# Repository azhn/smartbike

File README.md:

SMARTBIKE
=====

BLEES: Bluetooth Low Energy Environment Sensors.
<br /><br />
BLEES is a 1 inch round sensor tag for sensing the ambient environment. It monitors
temperature, humidity, light, pressure, and movement and reports its readings
over BLE.
<br /><br /><br />

Hardware
--------
The BLEES hardware is a small, once inch round sensor board that mounts onto a [Squall](https://github.com/helena-project/squall) BLE sensor tag. The board 
currently has four sensors:

1. Temperature and Humidity
2. Pressure
3. Light
4. Accelerometer

The BLEES hardware is located in the `hardware` directory, where you can find
the Eagle design files.

Software
--------
The [Squall](https://github.com/helena-project/squall) uses the software located 
in the `software` directory. Follow the directions at [Lab11's Wiki](http://lab11.eecs.umich.edu/wiki/doku.php?id=eecs582w15:setup:start) to 
get your machine set up to build and flash the Squall.

The software sends out the data from the BLEES sensors in BLE advertisements. Specifically,
we encode the data in the "manufacturer data" section of a BLE advertisement and scan response packet.
This means that we do not have to establish a connection between the Squall and a scanning device, 
saving energy by not requiring any devices to pair with the BLEES device, and allowing us to send
the sensor data to many different scanning devices at once.

[Here's a useful BLE Advertisement primer](http://www.argenox.com/bluetooth-low-energy-ble-v4-0-development/library/a-ble-advertising-primer/)

Summon App
-----------
[Summon](https://github.com/lab11/summon) is a UI application for BLE devices.
Rather than requiring every user
to install a new app for every BLE device, Summon allows BLE devices to
point to their own HTML/JS based interface and loads it in a single
application. BLEES supports the summon architecture and provides
a Summon application.

Cloning
-------
To clone both this repository and the required submodules,
clone with the `--recursive` option: 
`git clone --recursive git@github.com:lab11/blees.git`

Otherwise, you can initialize the submodule and keep submodules up to
date by doing `git submodule update --init --recursive`.

If you think all of this is ridiculous and git should just handle submodules automatically, use this:
https://gist.github.com/brghena/fc4483a2df83c47660a5

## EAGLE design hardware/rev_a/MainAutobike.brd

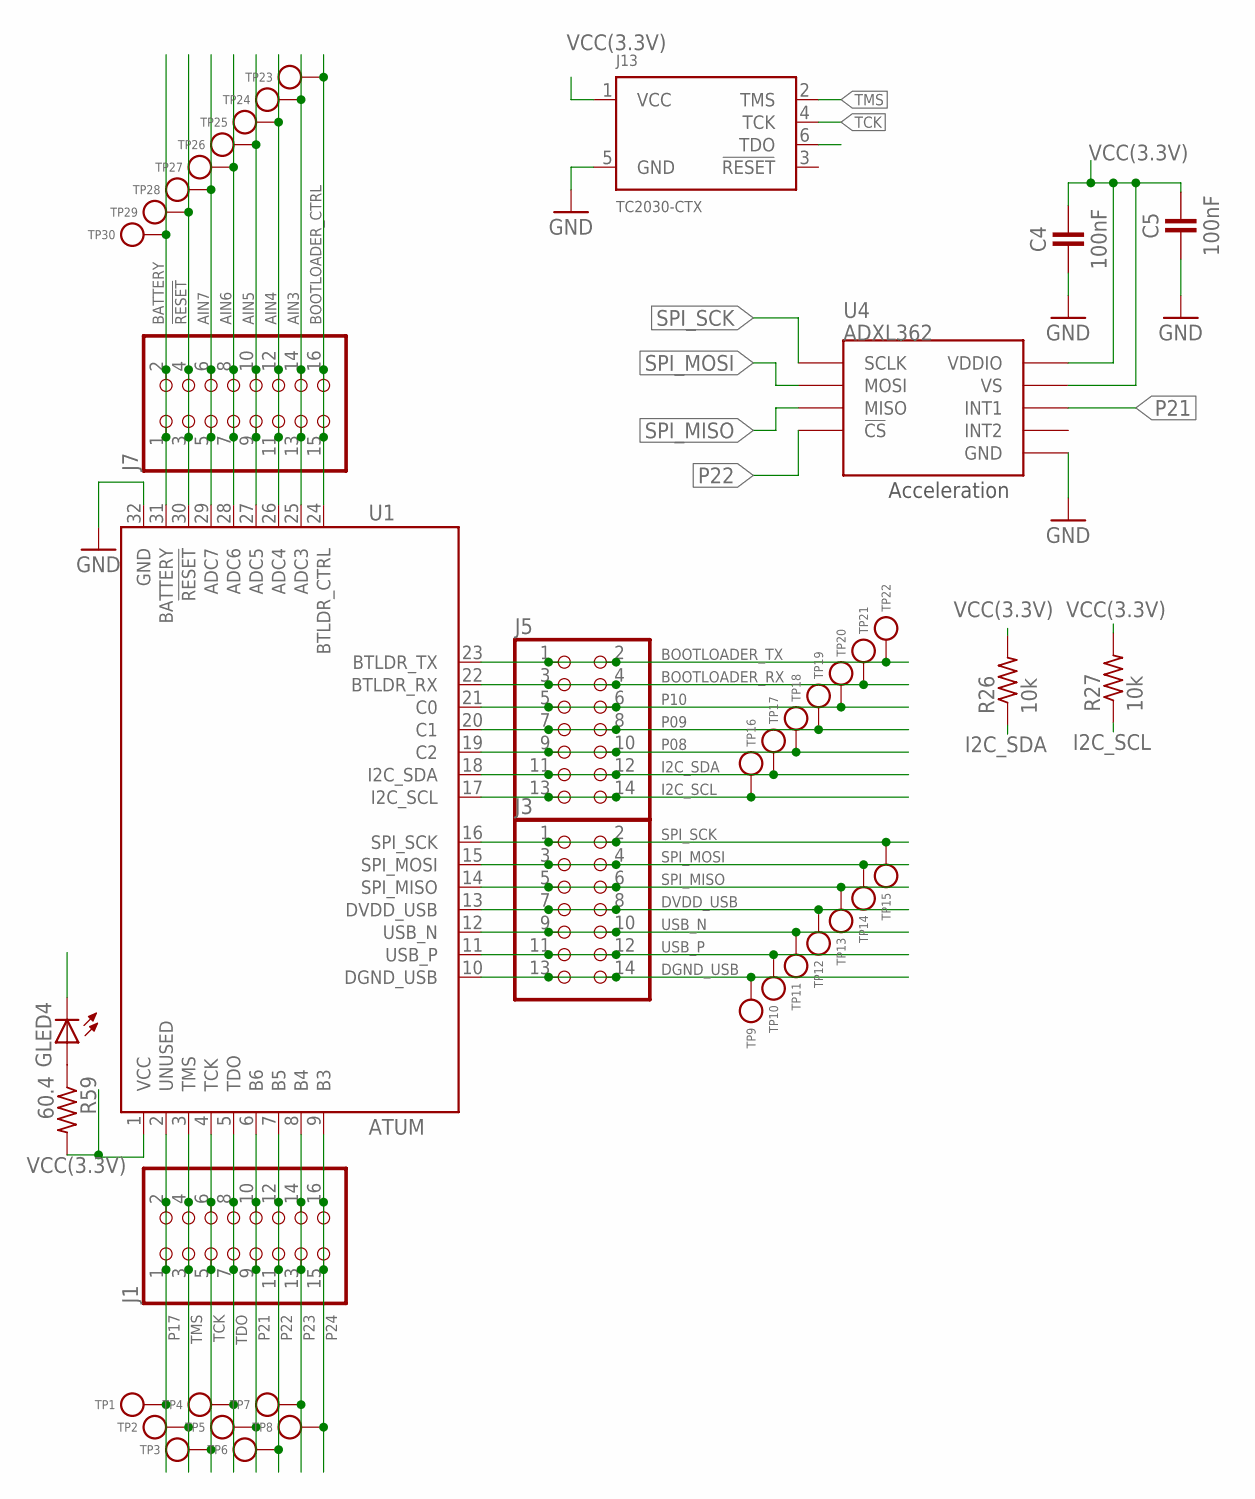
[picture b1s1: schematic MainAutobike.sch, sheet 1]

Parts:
C4, C5: 100nF; 0402_CAP
GLED4: LEDCHIP-LED0603; CHIP-LED0603
J1, J7: PINHD-2X8; 2X08; DIGIKEY 609-3364-ND
J3, J5: PINHD-2X7; 2X07; DIGIKEY 609-3491-ND
J13: TC2030-CTX; TC2030-IDC
R26, R27: 10k; R0603
R59: 60.4; R0402
TP1, TP2, TP3, TP4, TP5, TP6, TP7, TP8, TP9, TP10, TP11, TP12, TP13, TP14, TP15, TP16, TP17, TP18, TP19, TP20, TP21, TP22, TP23, TP24, TP25, TP26, TP27, TP28, TP29, TP30: TEST_POINT_0.040IN; TESTPOINT_0.040IN
U1: ATUM
U4: ADXL362

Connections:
!RESET: J7.3, J7.4, TP29.TESTPOINT, U1.30 (!RESET)
AIN3: J7.13, J7.14, TP24.TESTPOINT, U1.25 (ADC3); also elsewhere on the board
AIN4: J7.11, J7.12, TP25.TESTPOINT, U1.26 (ADC4); also elsewhere on the board
AIN5: J7.9, J7.10, TP26.TESTPOINT, U1.27 (ADC5); also elsewhere on the board
AIN6: J7.7, J7.8, TP27.TESTPOINT, U1.28 (ADC6); also elsewhere on the board
AIN7: J7.5, J7.6, TP28.TESTPOINT, U1.29 (ADC7); also elsewhere on the board
BATTERY: J7.1, J7.2, TP30.TESTPOINT, U1.31 (BATTERY)
BOOTLOADER_CTRL: J7.15, J7.16, TP23.TESTPOINT, U1.24 (BTLDR_CTRL)
BOOTLOADER_RX: J5.3, J5.4, TP21.TESTPOINT, U1.22 (BTLDR_RX)
BOOTLOADER_TX: J5.1, J5.2, TP22.TESTPOINT, U1.23 (BTLDR_TX)
DGND_USB: J3.13, J3.14, TP9.TESTPOINT, U1.10 (DGND_USB)
DVDD_USB: J3.7, J3.8, TP12.TESTPOINT, U1.13 (DVDD_USB)
GND: C4.2, C5.2, GLED4.C, J13.5 (GND), U1.32 (GND), U4.P$12 (GND), U4.P$13 (GND), U4.P$16 (GND); also elsewhere on the board
I2C_SCL: J5.13, J5.14, R27.1, TP16.TESTPOINT, U1.17 (I2C_SCL); also elsewhere on the board
I2C_SDA: J5.11, J5.12, R26.1, TP17.TESTPOINT, U1.18 (I2C_SDA); also elsewhere on the board
unnamed: GLED4.A, R59.1
P08: J5.9, J5.10, TP18.TESTPOINT, U1.19 (C2)
P09: J5.7, J5.8, TP19.TESTPOINT, U1.20 (C1); also elsewhere on the board
P10: J5.5, J5.6, TP20.TESTPOINT, U1.21 (C0); also elsewhere on the board
P17: J1.1, J1.2, TP1.TESTPOINT, U1.2 (UNUSED)
P21: J1.9, J1.10, TP5.TESTPOINT, U1.6 (B6), U4.P$11 (INT1)
P22: J1.11, J1.12, TP6.TESTPOINT, U1.7 (B5), U4.P$8 (!CS)
P23: J1.13, J1.14, TP7.TESTPOINT, U1.8 (B4)
P24: J1.15, J1.16, TP8.TESTPOINT, U1.9 (B3)
SPI_MISO: J3.5, J3.6, TP13.TESTPOINT, U1.14 (SPI_MISO), U4.P$7 (MISO)
SPI_MOSI: J3.3, J3.4, TP14.TESTPOINT, U1.15 (SPI_MOSI), U4.P$6 (MOSI)
SPI_SCK: J3.1, J3.2, TP15.TESTPOINT, U1.16 (SPI_SCK), U4.P$4 (SCLK)
TCK: J1.5, J1.6, J13.4 (TCK), TP3.TESTPOINT, U1.4 (TCK)
TDO: J1.7, J1.8, J13.6 (TDO), TP4.TESTPOINT, U1.5 (TDO)
TMS: J1.3, J1.4, J13.2 (TMS), TP2.TESTPOINT, U1.3 (TMS)
USB_N: J3.9, J3.10, TP11.TESTPOINT, U1.12 (USB_N)
USB_P: J3.11, J3.12, TP10.TESTPOINT, U1.11 (USB_P)
VCC(3.3V): C4.1, C5.1, J13.1 (VCC), R26.2, R27.2, R59.2, U1.1 (VCC), U4.P$1 (VDDIO), U4.P$14 (VS); also elsewhere on the board

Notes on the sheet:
Acceleration

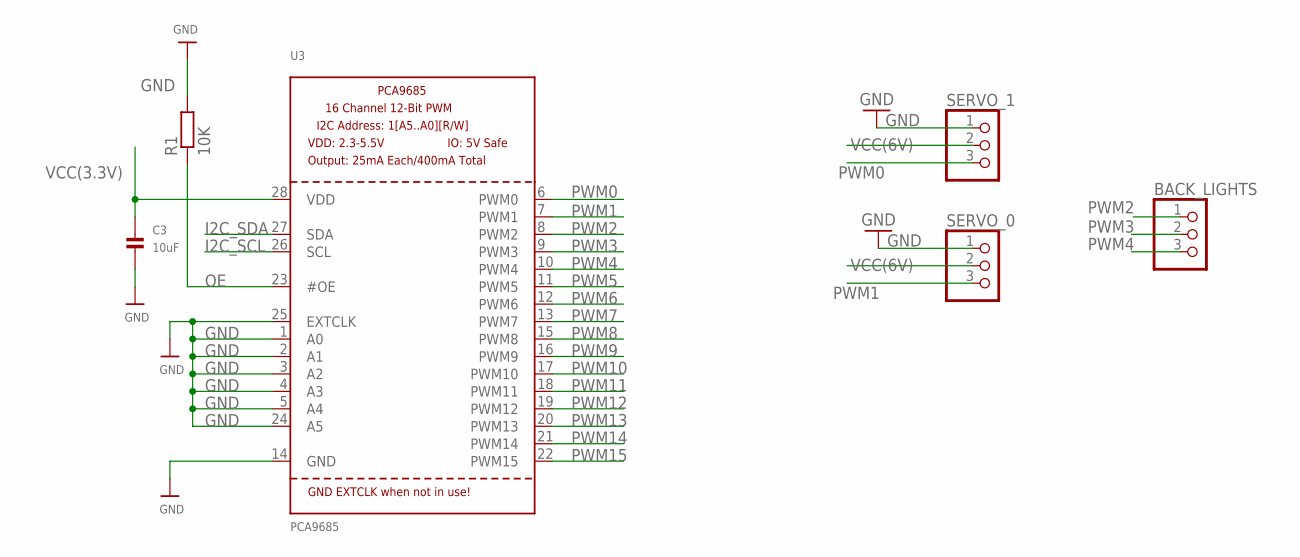
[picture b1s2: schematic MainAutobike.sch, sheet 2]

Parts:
BACK_LIGHTS: PINHD-1X3; 1X03
C3: 10uF; 0805
R1: 10K; R0603
SERVO_0, SERVO_1: PINHD-1X3; 1X03
U3: PCA9685; TSSOP28

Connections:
GND: C3.2, R1.2, SERVO_0.1, SERVO_1.1, U3.1 (A0), U3.2 (A1), U3.3 (A2), U3.4 (A3), U3.5 (A4), U3.14 (GND), U3.24 (A5), U3.25 (EXTCLK); also elsewhere on the board
I2C_SCL: U3.26 (SCL); also elsewhere on the board
I2C_SDA: U3.27 (SDA); also elsewhere on the board
OE: R1.1, U3.23 (#OE)
PWM0: SERVO_1.3, U3.6 (PWM0)
PWM1: SERVO_0.3, U3.7 (PWM1)
PWM2: BACK_LIGHTS.1, U3.8 (PWM2)
PWM3: BACK_LIGHTS.2, U3.9 (PWM3)
PWM4: BACK_LIGHTS.3, U3.10 (PWM4)
PWM5: U3.11 (PWM5)
PWM6: U3.12 (PWM6)
PWM7: U3.13 (PWM7)
PWM8: U3.15 (PWM8)
PWM9: U3.16 (PWM9)
PWM10: U3.17 (PWM10)
PWM11: U3.18 (PWM11)
PWM12: U3.19 (PWM12)
PWM13: U3.20 (PWM13)
PWM14: U3.21 (PWM14)
PWM15: U3.22 (PWM15)
VCC(3.3V): C3.1, U3.28 (VDD); also elsewhere on the board
VCC(6V): SERVO_0.2, SERVO_1.2; also elsewhere on the board

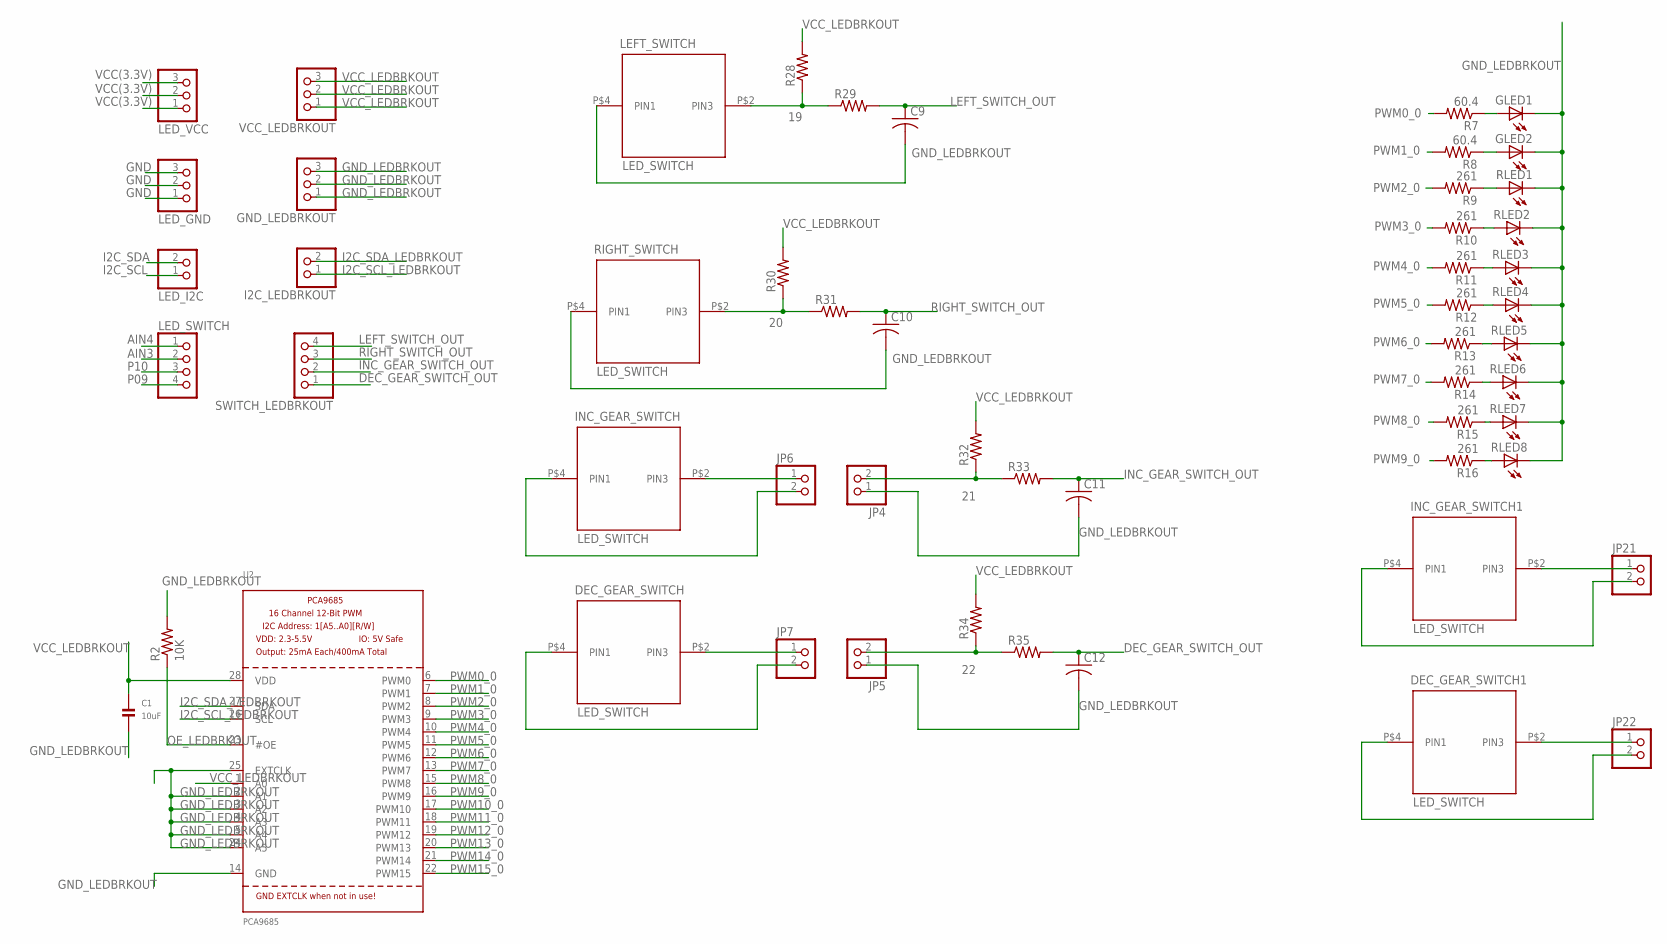
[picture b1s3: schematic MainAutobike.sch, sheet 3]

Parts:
C1: 10uF; 0805
C9, C10, C11, C12: C-USC0402; C0402
DEC_GEAR_SWITCH, DEC_GEAR_SWITCH1: LED_SWITCH
GLED1, GLED2: LEDCHIP-LED0603; CHIP-LED0603
GND_LEDBRKOUT: PINHD-1X3; 1X03
I2C_LEDBRKOUT: PINHD-1X2; 1X02
INC_GEAR_SWITCH, INC_GEAR_SWITCH1: LED_SWITCH
JP4, JP5, JP6, JP7, JP21, JP22: PINHD-1X2; 1X02
LED_GND: PINHD-1X3; 1X03
LED_I2C: PINHD-1X2; 1X02
LED_SWITCH: PINHD-1X4; 1X04
LED_VCC: PINHD-1X3; 1X03
LEFT_SWITCH: LED_SWITCH
R2: 10K; R0603
R7, R8: 60.4; R0402
R9, R10, R11, R12, R13, R14, R15, R16: 261; R0402
R28, R29, R30, R31, R32, R33, R34, R35: R-US_R0402; R0402
RIGHT_SWITCH: LED_SWITCH
RLED1, RLED2, RLED3, RLED4, RLED5, RLED6, RLED7, RLED8: LEDCHIP-LED0603; CHIP-LED0603
SWITCH_LEDBRKOUT: PINHD-1X4; 1X04
U2: PCA9685; TSSOP28
VCC_LEDBRKOUT: PINHD-1X3; 1X03

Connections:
19: LEFT_SWITCH.P$2 (PIN3), R28.1, R29.1
20: R30.1, R31.1, RIGHT_SWITCH.P$2 (PIN3)
21: JP4.2, R32.1, R33.1
22: JP5.2, R34.1, R35.1
AIN3: LED_SWITCH.2; also elsewhere on the board
AIN4: LED_SWITCH.1; also elsewhere on the board
DEC_GEAR_SWITCH_OUT: C12.1, R35.2, SWITCH_LEDBRKOUT.1
GND: LED_GND.1, LED_GND.2, LED_GND.3; also elsewhere on the board
GND_LEDBRKOUT: C1.2, C9.2, C10.2, C11.2, C12.2, GLED1.C, GLED2.C, GND_LEDBRKOUT.1, GND_LEDBRKOUT.2, GND_LEDBRKOUT.3, JP4.1, JP5.1, LEFT_SWITCH.P$4 (PIN1), R2.2, RIGHT_SWITCH.P$4 (PIN1), RLED1.C, RLED2.C, RLED3.C, RLED4.C, RLED5.C, RLED6.C, RLED7.C, RLED8.C, U2.2 (A1), U2.3 (A2), U2.4 (A3), U2.5 (A4), U2.14 (GND), U2.24 (A5), U2.25 (EXTCLK)
I2C_SCL: LED_I2C.1; also elsewhere on the board
I2C_SCL_LEDBRKOUT: I2C_LEDBRKOUT.1, U2.26 (SCL)
I2C_SDA: LED_I2C.2; also elsewhere on the board
I2C_SDA_LEDBRKOUT: I2C_LEDBRKOUT.2, U2.27 (SDA)
INC_GEAR_SWITCH_OUT: C11.1, R33.2, SWITCH_LEDBRKOUT.2
LEFT_SWITCH_OUT: C9.1, R29.2, SWITCH_LEDBRKOUT.4
unnamed: R16.1, RLED8.A
unnamed: R15.1, RLED7.A
unnamed: R14.1, RLED6.A
unnamed: R13.1, RLED5.A
unnamed: R12.1, RLED4.A
unnamed: R11.1, RLED3.A
unnamed: R10.1, RLED2.A
unnamed: R9.1, RLED1.A
unnamed: GLED2.A, R8.1
unnamed: GLED1.A, R7.1
unnamed: INC_GEAR_SWITCH.P$4 (PIN1), JP6.2
unnamed: INC_GEAR_SWITCH.P$2 (PIN3), JP6.1
unnamed: DEC_GEAR_SWITCH.P$4 (PIN1), JP7.2
unnamed: DEC_GEAR_SWITCH.P$2 (PIN3), JP7.1
unnamed: INC_GEAR_SWITCH1.P$4 (PIN1), JP21.2
unnamed: INC_GEAR_SWITCH1.P$2 (PIN3), JP21.1
unnamed: DEC_GEAR_SWITCH1.P$4 (PIN1), JP22.2
unnamed: DEC_GEAR_SWITCH1.P$2 (PIN3), JP22.1
OE_LEDBRKOUT: R2.1, U2.23 (#OE)
P09: LED_SWITCH.4; also elsewhere on the board
P10: LED_SWITCH.3; also elsewhere on the board
PWM0_0: R7.2, U2.6 (PWM0)
PWM1_0: R8.2, U2.7 (PWM1)
PWM2_0: R9.2, U2.8 (PWM2)
PWM3_0: R10.2, U2.9 (PWM3)
PWM4_0: R11.2, U2.10 (PWM4)
PWM5_0: R12.2, U2.11 (PWM5)
PWM6_0: R13.2, U2.12 (PWM6)
PWM7_0: R14.2, U2.13 (PWM7)
PWM8_0: R15.2, U2.15 (PWM8)
PWM9_0: R16.2, U2.16 (PWM9)
PWM10_0: U2.17 (PWM10)
PWM11_0: U2.18 (PWM11)
PWM12_0: U2.19 (PWM12)
PWM13_0: U2.20 (PWM13)
PWM14_0: U2.21 (PWM14)
PWM15_0: U2.22 (PWM15)
RIGHT_SWITCH_OUT: C10.1, R31.2, SWITCH_LEDBRKOUT.3
VCC(3.3V): LED_VCC.1, LED_VCC.2, LED_VCC.3; also elsewhere on the board
VCC_LEDBRKOUT: C1.1, R28.2, R30.2, R32.2, R34.2, U2.1 (A0), U2.28 (VDD), VCC_LEDBRKOUT.1, VCC_LEDBRKOUT.2, VCC_LEDBRKOUT.3

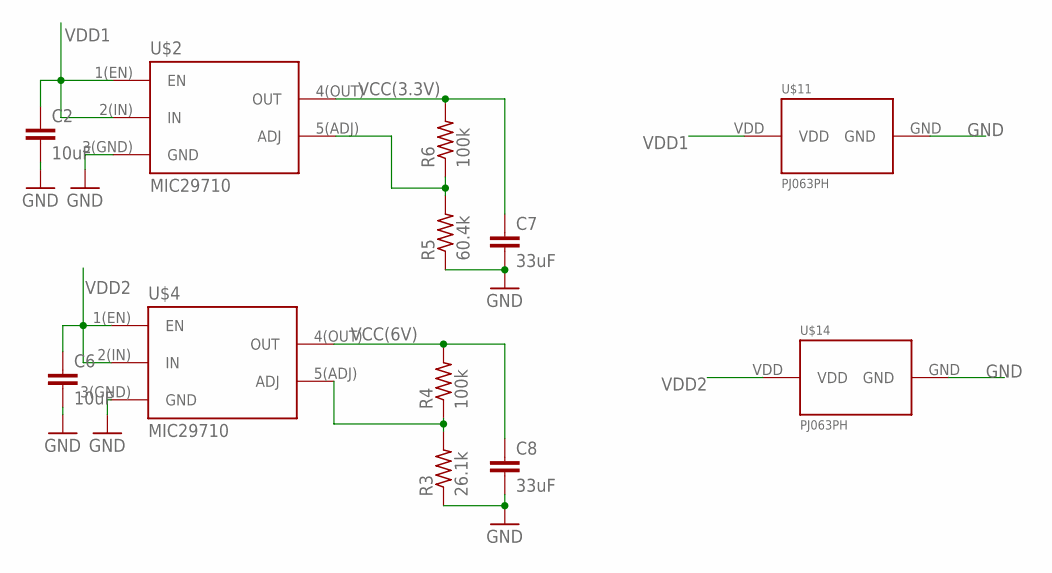
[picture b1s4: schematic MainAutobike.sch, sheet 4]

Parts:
C2, C6: 10uF; C0805
C7, C8: 33uF; C0805
R3: 26.1k; R0402
R4, R6: 100k; R0402
R5: 60.4k; R0402
U$2, U$4: MIC29710
U$11, U$14: PJ063PH; PJ063BH

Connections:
GND: C2.2, C6.2, C7.2, C8.2, R3.1, R5.1, U$2.3(GND) (GND), U$4.3(GND) (GND), U$11.GND, U$14.GND; also elsewhere on the board
unnamed: R5.2, R6.1, U$2.5(ADJ) (ADJ)
unnamed: R3.2, R4.1, U$4.5(ADJ) (ADJ)
VCC(3.3V): C7.1, R6.2, U$2.4(OUT) (OUT); also elsewhere on the board
VCC(6V): C8.1, R4.2, U$4.4(OUT) (OUT); also elsewhere on the board
VDD1: C2.1, U$2.1(EN) (EN), U$2.2(IN) (IN), U$11.VDD
VDD2: C6.1, U$4.1(EN) (EN), U$4.2(IN) (IN), U$14.VDD

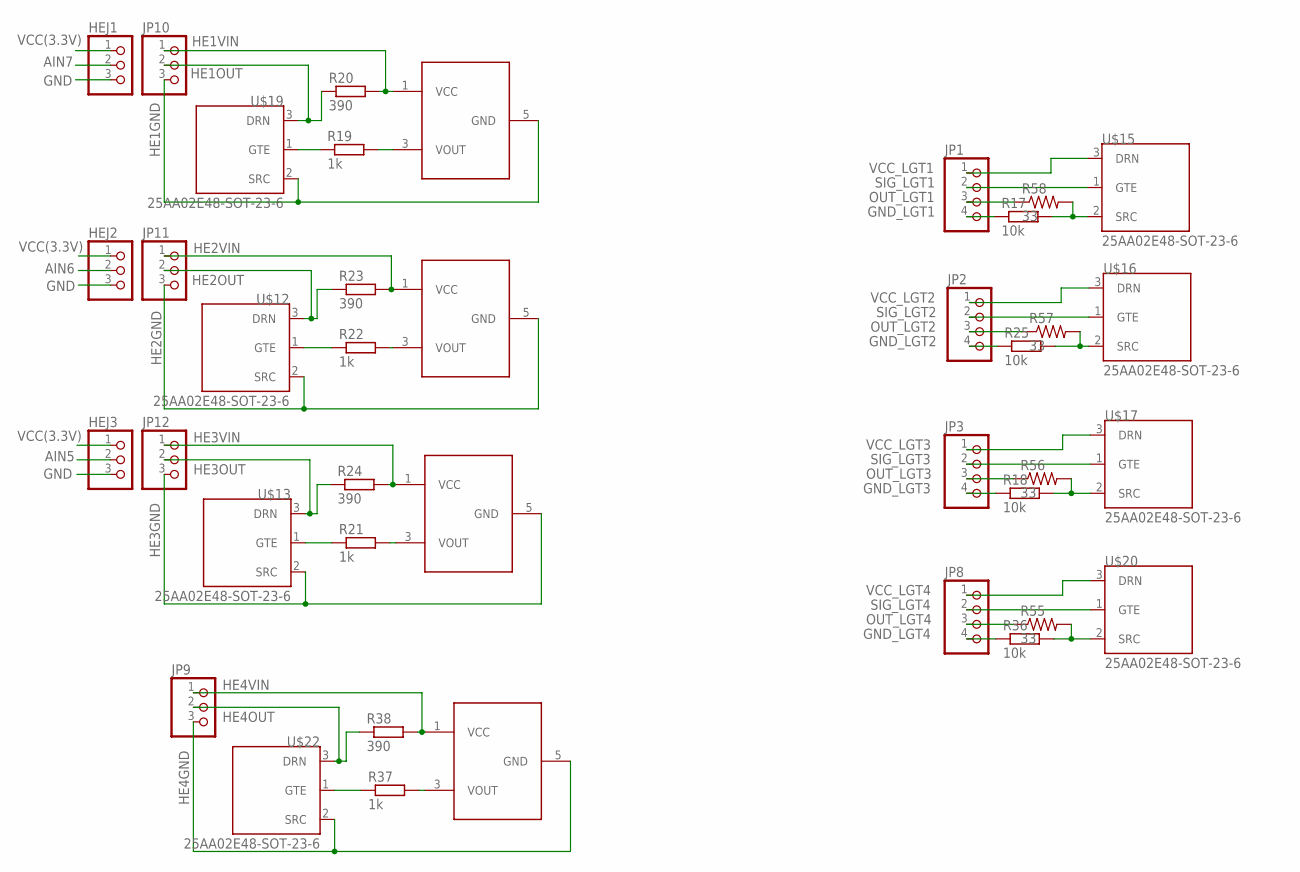
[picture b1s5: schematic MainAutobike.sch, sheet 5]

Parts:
HEJ1, HEJ2, HEJ3: PINHD-1X3; 1X03
JP1, JP2, JP3, JP8: PINHD-1X4; 1X04
JP9, JP10, JP11, JP12: PINHD-1X3; 1X03
R17, R18, R25, R36: 10k; R0603
R19, R21, R22, R37: 1k; R0603
R20, R23, R24, R38: 390; R0603
R55, R56, R57, R58: 33; R0402
U$5, U$6, U$18, U$21: HALLEFFECT; SOT23-6
U$12, U$13, U$15, U$16, U$17, U$19, U$20, U$22: 25AA02E48-SOT-23-6; SOT23-3

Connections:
AIN5: HEJ3.2; also elsewhere on the board
AIN6: HEJ2.2; also elsewhere on the board
AIN7: HEJ1.2; also elsewhere on the board
GND: HEJ1.3, HEJ2.3, HEJ3.3; also elsewhere on the board
GND_LGT1: JP1.4, R17.1
GND_LGT2: JP2.4, R25.1
GND_LGT3: JP3.4, R18.1
GND_LGT4: JP8.4, R36.1
HE1GND: JP10.3, U$18.5 (GND), U$19.2 (SRC)
HE1OUT: JP10.2, R20.1, U$19.3 (DRN)
HE1VIN: JP10.1, R20.2, U$18.1 (VCC)
HE2GND: JP11.3, U$5.5 (GND), U$12.2 (SRC)
HE2OUT: JP11.2, R23.1, U$12.3 (DRN)
HE2VIN: JP11.1, R23.2, U$5.1 (VCC)
HE3GND: JP12.3, U$6.5 (GND), U$13.2 (SRC)
HE3OUT: JP12.2, R24.1, U$13.3 (DRN)
HE3VIN: JP12.1, R24.2, U$6.1 (VCC)
HE4GND: JP9.3, U$21.5 (GND), U$22.2 (SRC)
HE4OUT: JP9.2, R38.1, U$22.3 (DRN)
HE4VIN: JP9.1, R38.2, U$21.1 (VCC)
unnamed: R37.1, U$22.1 (GTE)
unnamed: R37.2, U$21.3 (VOUT)
unnamed: R19.1, U$19.1 (GTE)
unnamed: R19.2, U$18.3 (VOUT)
unnamed: R21.1, U$13.1 (GTE)
unnamed: R21.2, U$6.3 (VOUT)
unnamed: R22.1, U$12.1 (GTE)
unnamed: R22.2, U$5.3 (VOUT)
unnamed: JP8.3, R55.1
unnamed: JP3.3, R56.1
unnamed: JP2.3, R57.1
unnamed: JP1.3, R58.1
OUT_LGT1: R17.2, R58.2, U$15.2 (SRC)
OUT_LGT2: R25.2, R57.2, U$16.2 (SRC)
OUT_LGT3: R18.2, R56.2, U$17.2 (SRC)
OUT_LGT4: R36.2, R55.2, U$20.2 (SRC)
SIG_LGT1: JP1.2, U$15.1 (GTE)
SIG_LGT2: JP2.2, U$16.1 (GTE)
SIG_LGT3: JP3.2, U$17.1 (GTE)
SIG_LGT4: JP8.2, U$20.1 (GTE)
VCC(3.3V): HEJ1.1, HEJ2.1, HEJ3.1; also elsewhere on the board
VCC_LGT1: JP1.1, U$15.3 (DRN)
VCC_LGT2: JP2.1, U$16.3 (DRN)
VCC_LGT3: JP3.1, U$17.3 (DRN)
VCC_LGT4: JP8.1, U$20.3 (DRN)

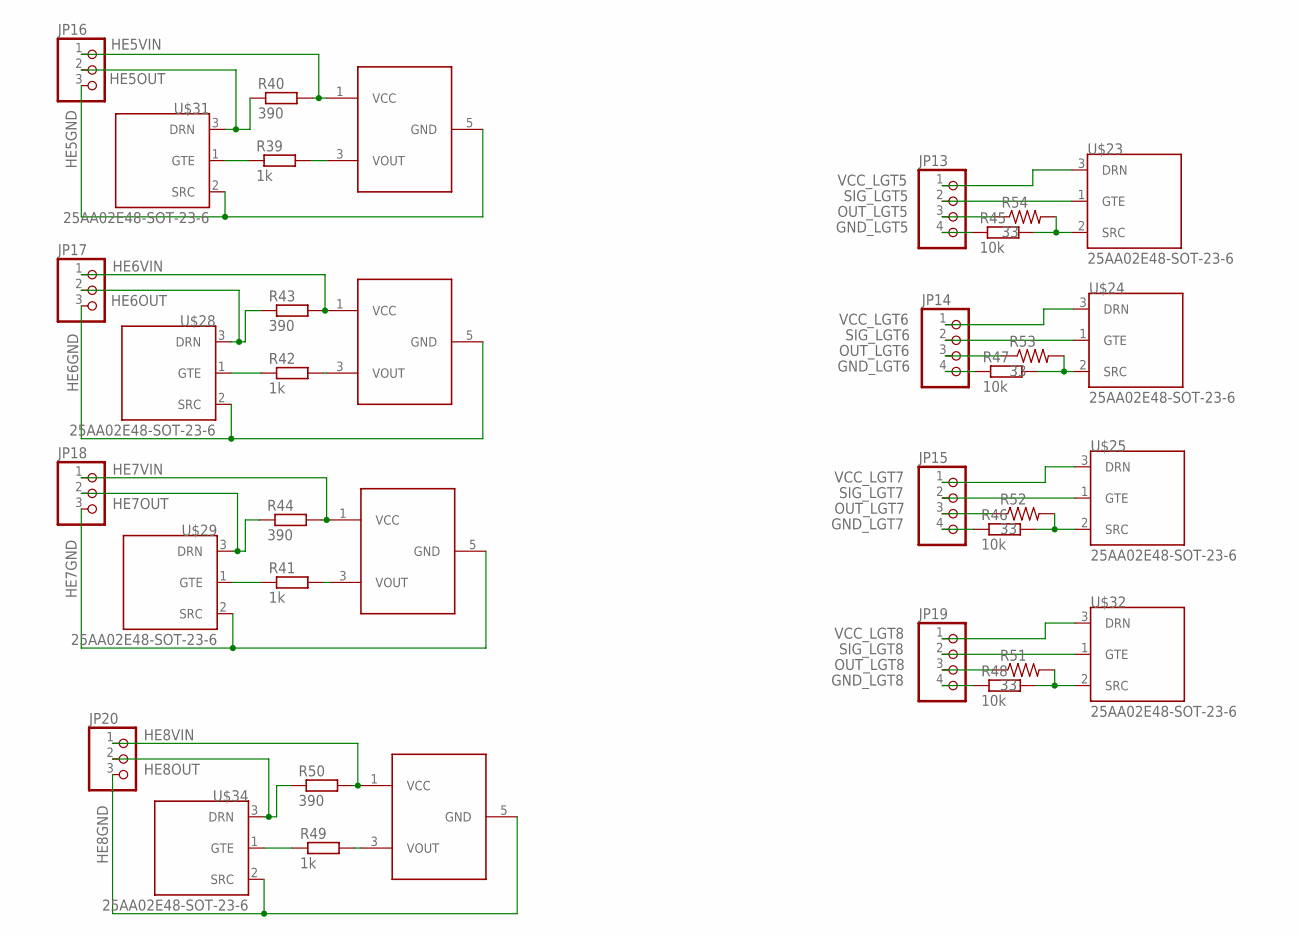
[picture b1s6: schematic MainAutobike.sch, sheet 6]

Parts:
JP13, JP14, JP15, JP19: PINHD-1X4; 1X04
JP16, JP17, JP18, JP20: PINHD-1X3; 1X03
R39, R41, R42, R49: 1k; R0603
R40, R43, R44, R50: 390; R0603
R45, R46, R47, R48: 10k; R0603
R51, R52, R53, R54: 33; R0402
U$23, U$24, U$25, U$28, U$29, U$31, U$32, U$34: 25AA02E48-SOT-23-6; SOT23-3
U$26, U$27, U$30, U$33: HALLEFFECT; SOT23-6

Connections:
GND_LGT5: JP13.4, R45.1
GND_LGT6: JP14.4, R47.1
GND_LGT7: JP15.4, R46.1
GND_LGT8: JP19.4, R48.1
HE5GND: JP16.3, U$30.5 (GND), U$31.2 (SRC)
HE5OUT: JP16.2, R40.1, U$31.3 (DRN)
HE5VIN: JP16.1, R40.2, U$30.1 (VCC)
HE6GND: JP17.3, U$26.5 (GND), U$28.2 (SRC)
HE6OUT: JP17.2, R43.1, U$28.3 (DRN)
HE6VIN: JP17.1, R43.2, U$26.1 (VCC)
HE7GND: JP18.3, U$27.5 (GND), U$29.2 (SRC)
HE7OUT: JP18.2, R44.1, U$29.3 (DRN)
HE7VIN: JP18.1, R44.2, U$27.1 (VCC)
HE8GND: JP20.3, U$33.5 (GND), U$34.2 (SRC)
HE8OUT: JP20.2, R50.1, U$34.3 (DRN)
HE8VIN: JP20.1, R50.2, U$33.1 (VCC)
unnamed: R39.1, U$31.1 (GTE)
unnamed: R39.2, U$30.3 (VOUT)
unnamed: R41.1, U$29.1 (GTE)
unnamed: R41.2, U$27.3 (VOUT)
unnamed: R42.1, U$28.1 (GTE)
unnamed: R42.2, U$26.3 (VOUT)
unnamed: R49.1, U$34.1 (GTE)
unnamed: R49.2, U$33.3 (VOUT)
unnamed: JP19.3, R51.1
unnamed: JP15.3, R52.1
unnamed: JP14.3, R53.1
unnamed: JP13.3, R54.1
OUT_LGT5: R45.2, R54.2, U$23.2 (SRC)
OUT_LGT6: R47.2, R53.2, U$24.2 (SRC)
OUT_LGT7: R46.2, R52.2, U$25.2 (SRC)
OUT_LGT8: R48.2, R51.2, U$32.2 (SRC)
SIG_LGT5: JP13.2, U$23.1 (GTE)
SIG_LGT6: JP14.2, U$24.1 (GTE)
SIG_LGT7: JP15.2, U$25.1 (GTE)
SIG_LGT8: JP19.2, U$32.1 (GTE)
VCC_LGT5: JP13.1, U$23.3 (DRN)
VCC_LGT6: JP14.1, U$24.3 (DRN)
VCC_LGT7: JP15.1, U$25.3 (DRN)
VCC_LGT8: JP19.1, U$32.3 (DRN)

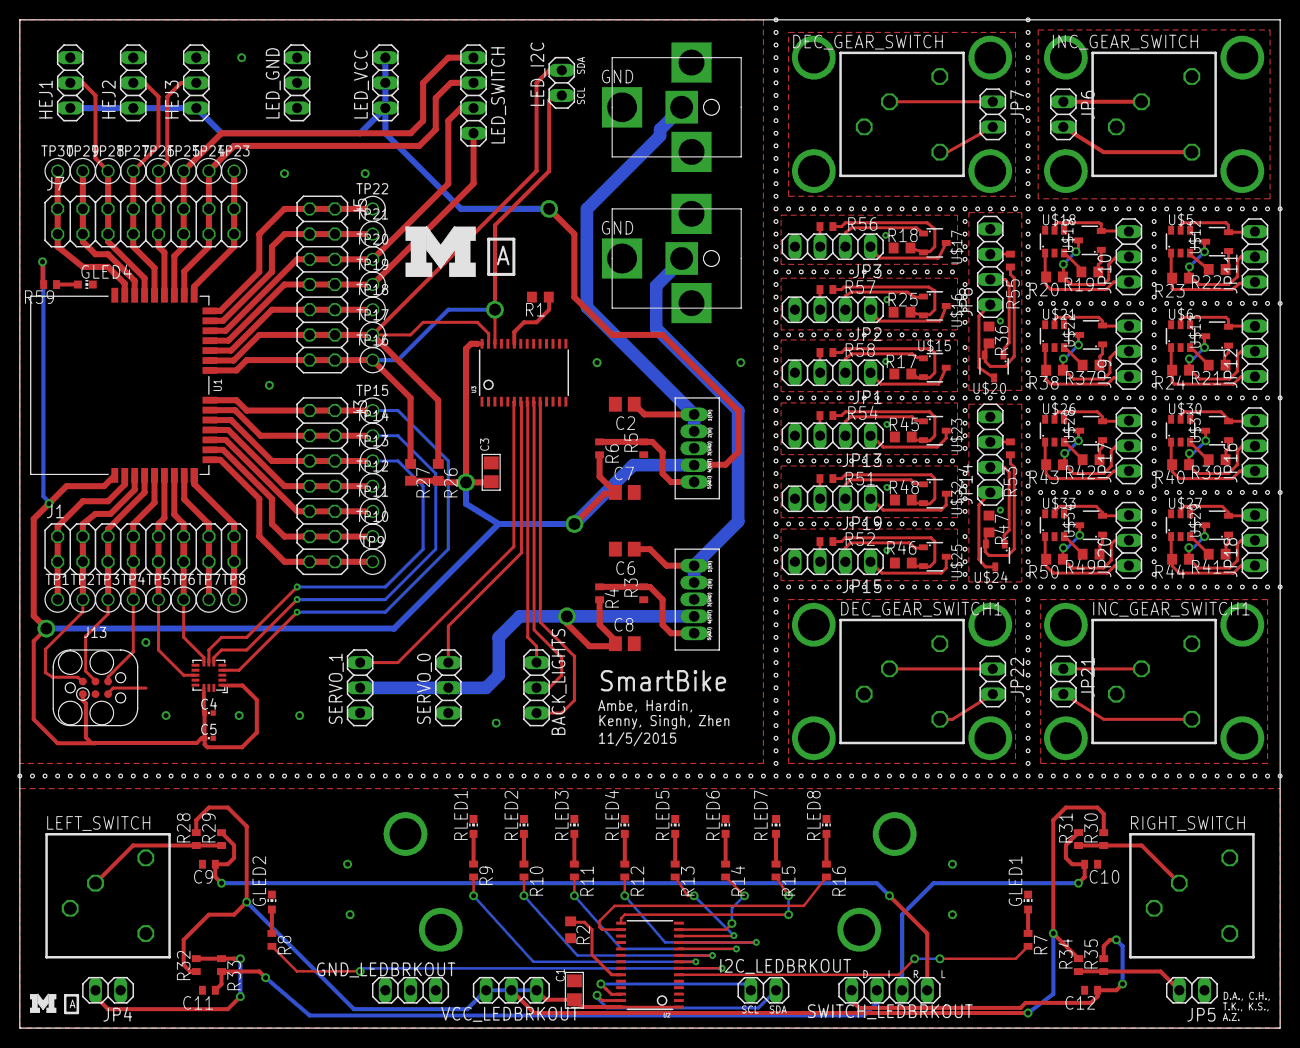
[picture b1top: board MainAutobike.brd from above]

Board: 2 copper layers, 127.0 x 101.6 mm, 193 parts (0 on the bottom side), 165 nets.

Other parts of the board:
U$1: UMICH_SOLID_200MIL
U$3: UMICH_SOLID_75MIL

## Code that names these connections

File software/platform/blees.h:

#ifndef BLEES_H
#define BLEES_H

#ifndef DEVICE_NAME
    #define DEVICE_NAME "BLEES"
#endif /*DEVICE_NAME*/

#include <stdint.h>

extern uint8_t MAC_ADDR[6];
#define PLATFORM_ID_BYTE 0x30

// Address is written here in flash if the ID command is used
#define ADDRESS_FLASH_LOCATION 0x0003fff8

// FTDI chip for bootloader
#define BOOTLOADER_CTRL_PIN  3
#define BOOTLOADER_CTRL_PULL NRF_GPIO_PIN_PULLUP
#define BOOTLOADER_RX_PIN 28
#define BOOTLOADER_TX_PIN 29

// Blue led on squall
#define SQUALL_LED_PIN 13

// Blue led on BLEES
//#define BLEES_LED_PIN 25
#define LED_START      18
#define LED_0          18
#define LED_1          19
#define LED_2          20
#define LED_END	       20

// UART on squall
#define UART_RX_PIN 28
#define UART_TX_PIN 29

// I2C through headers
#define I2C_SCL_PIN 1
#define I2C_SDA_PIN 7

// SPI through headers
#define SPI_SCLK_PIN 0
#define SPI_MISO_PIN 29
#define SPI_MOSI_PIN 30

// Light sensor
#define TSL2560_IRQ_PIN 22

// Pressure sensor
#define LPS331AP_IRQ1_PIN 24
#define LPS331AP_IRQ2_PIN 23

// Accelerometer
#define ADXL362_CS_PIN 4
#define ADXL362_IRQ1_PIN 6
#define ADXL362_IRQ2_PIN 5

#endif /*BLEES_H*/

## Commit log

2015-10-19 header files
2015-10-19 accel stuff (not tested)
2015-10-19 ifndef and define for h files added
2015-10-19 GPIO pin assignments file created
2015-10-19 fixed accel fxns
2015-10-20 accelerometer working in blink/main.c timer handler
2015-10-20 moved testing accel to separate folder
2015-10-20 Accelerometer stuff and makefile stuff
2015-10-20 fixed all the stupid shit with folders
2015-10-29 button tests in progress, compiling
2015-10-30 Added another example for gpiote stuff
2015-10-30 gpiote working bitch
2015-11-03 Encoder stuff we worked on, even though we're not using it anymore...
2015-11-03 Removed EncoderControl stuff causing building errors
2015-11-03 gpio drivers coded, compiled, to be tested
2015-11-04 working on pwm
2015-11-05 coded complete gpio driver using GPIOTE_IRQHandler from nrf_drv_gpiote.c
2015-11-05 working accelerometer data ready interrupts
2015-11-06 pwm fully functional; rename platform/blees to platform/smartbike, may need to fix target in some apps/.../Makefile
2015-11-06 Somebody changed blees.h to smartbike.h -- Had to get everything to compile again by changing makefiles and .c .h files
2015-11-07 updated gpio interrupt temp stuff
2015-11-07 fixed gpio interrupt driver
2015-11-07 changed chips folder to drivers and updated Makefiles with this path
2015-11-07 updated pwm driver & working interrupt-based-pwm control
2015-11-07 added some accelerometer-gpio stuff
2015-11-08 fixed LED constant issue
2015-11-08 Cleanup and renaming of files to allow for compile
2015-11-08 multiple definitions of GPIOTE_IRQHandler, commented the one from smartbike/main.c to allow for compile
2015-11-08 Hall effects skeleton. Needs work and redesign
2015-11-08 working simple/inefficient accelerometer gpio tilt test for demo purposes only
2015-11-10 pcb should be done
2015-11-10 updated pcb, added pdfs
2015-11-10 charles, look over hall effect please; checked rest of schematic and board
2015-11-10 can change pwm via debounced button interrupts
2015-11-11 updated threshold algorithm for accel turn check
2015-11-11 backup of test_pwm_int
2015-11-11 minor changes and cleanup
2015-11-11 Created a driver to manage producing data from accelerometer with averaging
2015-11-11 added asserts to AccelDataDriver
2015-11-12 fixed AccelDataDriver compile errors. made brake light test
2015-11-12 Fixed all the bugs with AccelDataDrivers
2015-11-12 port interrupts working
2015-11-12 started template for gear shifting stuff
2015-11-13 final revision A of PCB
2015-11-13 cam files for pcb
2015-11-13 wrong drill cam processor, must use eagle7 version when running in eagle7
2015-11-13 stupid gerbers
2015-11-13 generated gerbers with eagle v6
2015-11-13 no ground on POWER led... Tim...
2015-11-13 crap...
2015-11-13 zip files of gerbers
2015-11-14 Minor changes
2015-11-14 used data averaging to do tilt. Need to test
2015-11-14 updated accel_gpio test
2015-11-14 updated to fix turn signal double button and toggle functionality
2015-11-14 gpio port events and ble advertising
2015-11-15 Arduino sketch for shifting controlled by hall effect. Took out brake lights becuase I have a cleaner way to do that, which avoids floats. Numbers still need slight tweaking. Works well in lab, needs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
2015-11-17 WORKING GPIO PORT INTERRUPTSSSSSSSSSSSSSSSSSSSSSSSSSSSSSSSSSS
2015-11-17 Fixed up LightControl file
2015-11-18 coded up light control. Need pwm code to be inserted where stated
2015-11-18 fixed functions for h file. need to code up c file
2015-11-20 Changed port gpio from 1 to 32 in all directories. updated gpio driver to work with port events.
2015-11-20 Small driver for Hall Effect handlers and speed calculations
2015-11-20 ServoControl has ported code form Arduino Sketch. LightControl.h is fixed
2015-11-20 Added pwm driver functions to both LightControl and ServoControl. Fixed a few visual bugs and compiles
2015-11-20 starting to test current functionality on nordic
2015-11-20 got bike-state ready
2015-11-20 added pwm and servo setup
2015-11-20 GPIO driver tested and works perfectly
2015-11-20 compiles after gpio driver changes
2015-11-20 State Machine Changes to test_accel_averaging, no testing, output incomplete
2015-11-21 rearranged driver files and started work on main smartbike app
2015-11-21 moved a few files. deleted common.h/.c
2015-11-21 fixed merge conflicts
2015-11-21 Fixed main to use gpio driver
2015-11-21 working on things
2015-11-21 Changed polarity of gpio inputs
2015-11-22 compiles
2015-11-22 Added all speed/shifting function calls to appropriate places
2015-11-22 added timer api for smartbike - includes get millisecond
2015-11-22 shifting ready for testing
2015-11-22 changed bike state to update light information being stored
2015-11-22 Functional changes to LightControl
2015-11-23 smartbike main changes to reflect pins, and led debugging. Also, there's a real flying bug in the lab. Watch out.
2015-11-23 bike state additions
2015-11-23 updated main timers stuff
2015-11-24 timer stuff has changed. main in smartbike not working.
2015-11-24 test_counter working with BikeTimers api
2015-11-24 servo speeds being tested. We found out we need to do overshoot with timer. Talk to Alan or Dinker
2015-11-24 some updates to accelerometer turn control driver and test
2015-11-24 LightAction defined. Kunjan needs a dependency
2015-11-24 LightAction defined. Kunjan needs it because of a dependency
2015-11-24 fixed accel turn control driver
2015-11-24 updated pins for accel SPI driver
2015-11-24 changed pwm to use i2c address as param
2015-11-24 PWM addresses for smartbike go in smartbike.h in platform/
2015-11-24 Light Control for Allen
2015-11-25 Light action for pulling
2015-11-25 shifting servos using new PWM api
2015-11-25 light control using latest PWM api
2015-11-25 alan will try to compile
2015-11-25 made states for turn signals
2015-11-25 fixed a small problem in light action
2015-11-25 lightcontrol changed defines for pwm addresses to make them more readable
2015-11-25 prototype coded
2015-11-25 updated light stuff so it compiles
2015-11-25 accel turning working
2015-11-27 redesigned the light drivers
2015-11-27 code complete
2015-11-27 LightAction LightControl Compiles
2015-11-27 added Light file includes. will test here
2015-11-28 Light Action worked for a long while until communication with PWM stopped working. Need to find out problem with test_lights/main.c
2015-11-28 added tested code form turn signals, accel data drivers, and light output
2015-11-29 Changed how we access pin mappings and flags
2015-11-29 todo
2015-11-29 changed how smartbike handles pin mappings
2015-12-01 Fixed my stupid light bugs
2015-12-01 fixed main
2015-12-01 made some additions to test
2015-12-01 todo lightcontrol.h
2015-12-02 Bug fixed to allow gpio driver to work with our main
2015-12-02 made correct pin mappings
2015-12-02 comment
2015-12-03 created init function to avoid forgetting to set axis polling
2015-12-03 fixed a bug where a rear light state was incorrect
2015-12-03 fixed a flag update bug. added initializePinsStatus which must be called after gpio init to fix a bug where port handler gets called on init and a turn light signal starts on
2015-12-03 tested lights
2015-12-03 light actions and control (turn, rear, gears) are currently integrated, tested, and working with smartbike main.
2015-12-03 changed pwm values
2015-12-04 added new functionality for turning in bikestate
2015-12-04 work in progress for AccelTurnControl. Delving work to Kunjan
2015-12-04 handle turn test
2015-12-04 ble manual setup test in apps/test_ble_app/
2015-12-04 abstracted some new turn hall effect control stuff (NEED TO CHANGE PINS)
2015-12-05 added accel timers
2015-12-05 example for using accel timer; all you have to do is call the set_accel_handler function with a function as the parameter before calling timers_init
2015-12-05 ignore accel if turn caused by bike handles, NEED TO ADD SPEED CHECK FOR ACCEL TILT TURN SIGNALS
2015-12-05 still working on ble, almost done with setup and initializing
2015-12-05 changed pullup and pulldown to nopull
2015-12-05 updated test_lights main
2015-12-05 All our timers added
2015-12-07 app scheduler tests(may be useful sometime); ble advertising with timers
2015-12-07 :fu: finally can advertise the damn csc service and see it on the nrf toolbox app
2015-12-07 added timer stuff for accel and light toggle
2015-12-07 changed pwm values for lgiht output
2015-12-07 working turn control with accelerometer and hall effects
2015-12-07 working lights, and turning in smartbike main
2015-12-08 stays connected, had to change softdevice clock init parameter
2015-12-08 starting cscs tests; can connect and advertise nonconnectably at same time
2015-12-08 WOOO! FAKE DATA PICKED UP ON APP!
2015-12-08 ble works with multiple timers
2015-12-09 removed asserts...all of them
2015-12-09 ble stuff ported to main and RAM-stack overflow issue fixed by removing assert library
2015-12-09 got stuff working on this branch with all gpio inputs
2015-12-09 changed servo arrays to appropriate numbers, added a check to make sure we cant attempt to shift to a gear that indexes out of the array.
2015-12-09 fixed ble timer by disabling turn signal timer (its too slow)
2015-12-09 remove accel ready from ble handler
2015-12-10 scaled get millis timer to work with BLE timer
2015-12-10 manual automatic mode stuff
2015-12-10 fixed merge bug
2015-12-10 make update gear check for manual or auto mode
2015-12-10 changes light
2015-12-10 works, don't touch it....can't touch this.....
2015-12-10 forgot a file... oops
2015-12-10 added real ble data to transmit
2015-12-10 changes to bikestate shifting pins. Changes to manual shifting in hall effect control
2015-12-10 saves speed
2015-12-10 incremental changes. No more light timer. integrated into accel timer with scaler. all functionality working.
2015-12-10 fixed a bug
2015-12-10 changes to ble broadcasting
2015-12-10 got braking to and shifting to work well.
2015-12-10 tuning
2015-12-12 Fixed eagle shematic merge conflict

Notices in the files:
parts and their libraries:
SparkFun-Sensors: Licensing: CC v3.0 Share-Alike You are welcome to use this library for commercial purposes.
